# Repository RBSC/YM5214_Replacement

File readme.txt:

--------------------------------------------------------------------------------
Yamaha YM5214 Emulator Board v1.0
Copyright (c) 2023-2026 RBSC
--------------------------------------------------------------------------------

About
-----

This project's goal was to emulate Yamaha's YM5214 MMC chip that is used in CX5M and similar MSX1 computers as a
memory controller. These chips start to fail in the recent years, so it's good to have an alternative to keep our
CX5Ms alive. The design of this circuit board was inspired by a similar project by MetalGear2, whose website can
be found here: http://mymsx2.free.fr/

Assembling and Installing
-------------------------

The board is relatively easy to assemble. Please make sure that you solder all necessary elements and then remove
all flux from the board. The Altera chip on the newly-assembled board must be programmed before use. To do that,
you need to buy a USB Blaster device that can be easily obtained from AliExpress and download the Quartus II
Programmer v15.0 software that can be downloaded from here:

https://sysadminmosaic.ru/en/quartus_ii/quartus_ii#quartusiiweb150

To successfully program the CPLD, you must supply 5 Volts to the board. This can be done using a standard USB-A
cable to which two wires with female Dupont-type connectors have been soldered instead of the miniUSB or microUSB
connector. A cable with broken miniUSB or MicroUSB connector will do fine.

To program the CPLD it is not necessary to solder the JTAG connector or a pin header to the board. It is sufficient
to insert a 2x5-pin header into the "female" connector of the USB Blaster programmer, plug it into the JTAG
connector on the board, and bend it slightly for better contact with the board.

To power the board connect +5V to pin 10 on the YM5214's pin header and connect GND (ground) to pin 1. After that
you can connect the USB Blaster to the JTAG connector. Mind the correct orientation! Now you are ready to program
the CPLD chip.

Select the JTAG mode in the Quartus Programmer software and click the Auto-Detect button. If everything is assembled
and connected correctly, Quartus will detect the EPM240 chip. Next, place the cursor onto the firmware control line
(the one with "EPM240" string), right-click, and select the "Change File" option. A file selection window will
appear. Locate the firmware you need: it can be found in the Firmware folder. Select the .POF file with the firmware
and open it. Set the "Program/Configure," "Verify," and "Blank check" options and click the "Start" button to start
programming.

The CPLD programming usually takes less than a minute. A sign of successful programming is when the progress bar
reaches 100% and no errors appear in the lower window of the user interface. Once the CPLD programming is complete,
first disconnect the programmer and then disconnect the power cable from the board. The board is now fully ready
for use.

To install the board into the CX5M, first remove the broken YM5214 chip and install a 40-pin socket. Do not use sockets
with round pins unless you soldered round pin headers onto the curcuit board. Then carefully insert the curcuit board
into the socket and make sure it sits there firmly. Mind the orientation of the board! When powered on, your CX5M
should boot up in Basic and show 28kb of available RAM if the board is working correctly.

If you are unsure how to interpret or follow the above instructions, then it's advised to ask a more experienced
person for help.

IMPORTANT!
----------

The RBSC provides all the files and information for free, without any liability (see the disclaimer.txt file). The
provided information, software or hardware must not be used for commercial purposes unless permitted by the RBSC.
Producing a small amount of bare boards for personal projects and selling the rest of the batch is allowed without
the permission of RBSC.

When the sources of the tools are used to create alternative projects, please always mention the original source and
the copyright!

Contact information
-------------------

The members of RBSC group Tnt23, Wierzbowsky, Pyhesty, Ptero, GreyWolf, SuperMax, VWarlock, ALSP and DJS3000 can be
contacted via the group's e-mail address:

info@rbsc.su

The group's coordinator could be reached via this e-mail address:

admin@rbsc.su

The group's website can be found here:

https://rbsc.su/
https://rbsc.su/ru

The RBSC's hardware repository can be found here:

https://github.com/rbsc

The RBSC's 3D model repository can be found here:

https://www.thingiverse.com/groups/rbsc/things

-= ! MSX FOREVER ! =-

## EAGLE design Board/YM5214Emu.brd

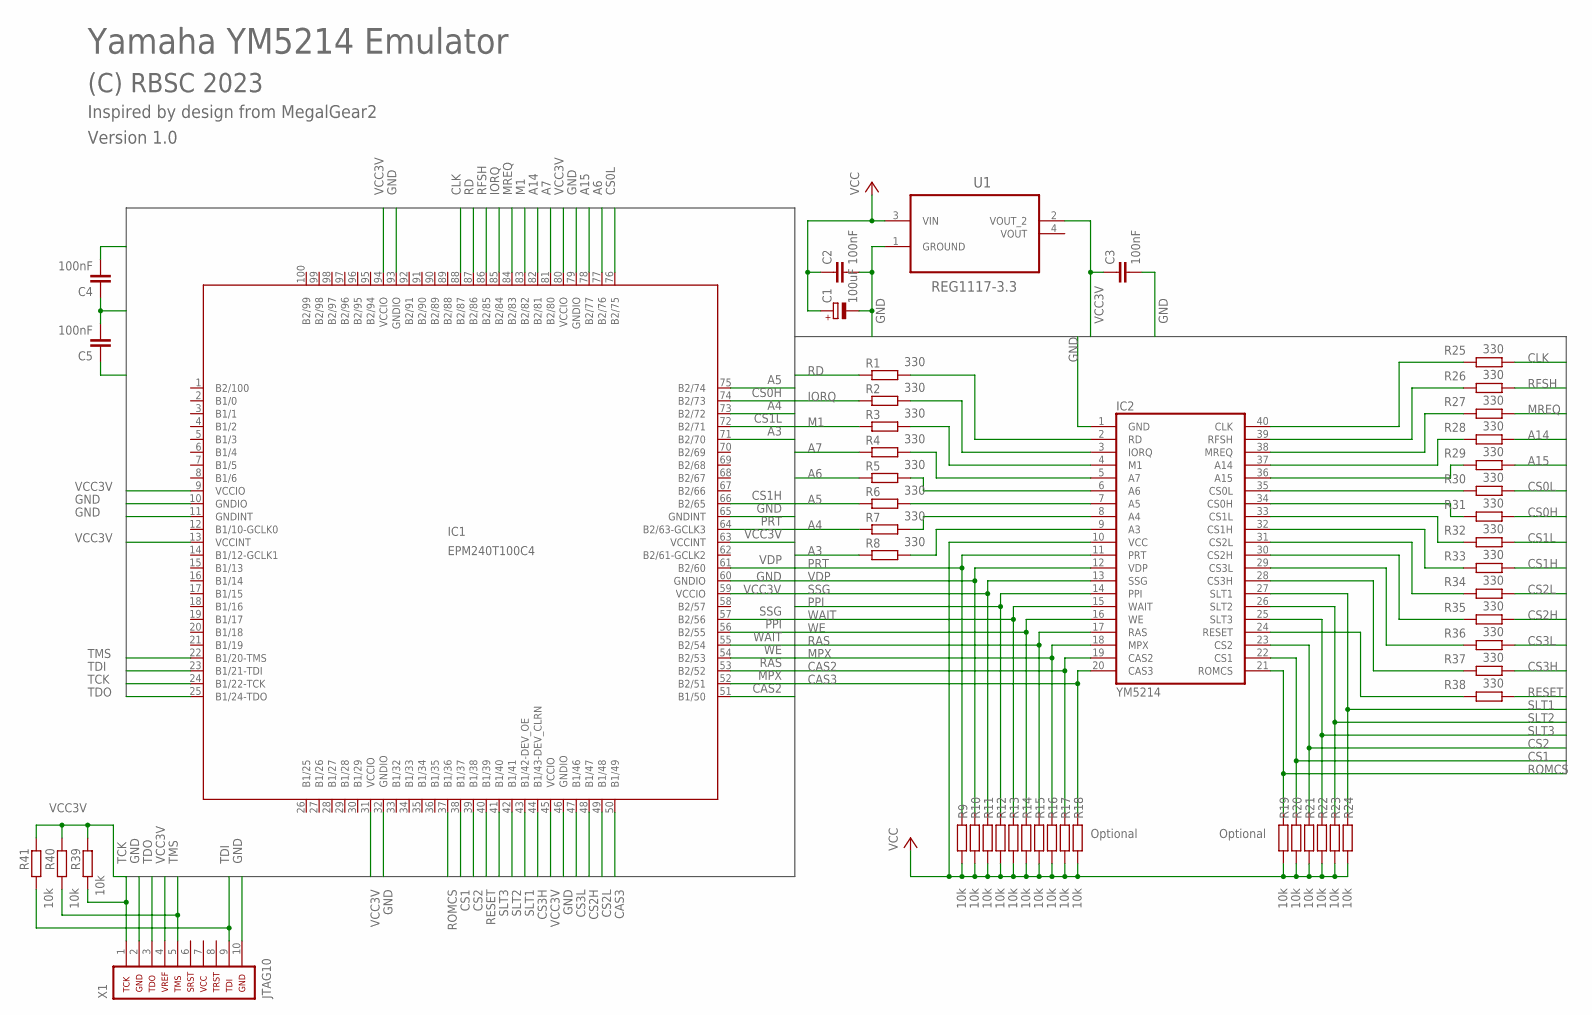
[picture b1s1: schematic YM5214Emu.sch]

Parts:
C1: 100uF; SMC_D
C2, C3, C4, C5: 100nF; C0805
IC1: EPM240T100C4; TQFP100
IC2: YM5214; DIL40
R1, R2, R3, R4, R5, R6, R7, R8, R25, R26, R27, R28, R29, R30, R31, R32, R33, R34, R35, R36, R37, R38: 330; R0805
R9, R10, R11, R12, R13, R14, R15, R16, R17, R18, R19, R20, R21, R22, R23, R24, R39, R40, R41: 10k; R0805
U1: REG1117-3.3; SOT230P700X180-4N
X1: JTAG10

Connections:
A3: IC1.71 (B2/70), R8.1
A4: IC1.73 (B2/72), R7.1
A5: IC1.75 (B2/74), R6.1
A6: IC1.77 (B2/76), R5.1
A7: IC1.81 (B2/80), R4.1
A14: IC1.82 (B2/81), R28.2
A15: IC1.78 (B2/77), R29.2
CAS2: IC1.51 (B1/50), IC2.19 (CAS2), R17.2
CAS3: IC1.50 (B1/49), IC2.20 (CAS3), R18.2
CLK: IC1.88 (B2/87), R25.2
CS0H: IC1.74 (B2/73), R31.2
CS0L: IC1.76 (B2/75), R30.2
CS1: IC1.38 (B1/37), IC2.22 (CS1), R20.2
CS1H: IC1.66 (B2/65), R33.2
CS1L: IC1.72 (B2/71), R32.2
CS2: IC1.39 (B1/38), IC2.23 (CS2), R21.2
CS2H: IC1.48 (B1/47), R35.2
CS2L: IC1.49 (B1/48), R34.2
CS3H: IC1.44 (B1/43-DEV_CLRN), R37.2
CS3L: IC1.47 (B1/46), R36.2
GND: C1.-, C2.2, C3.2, C4.1, C5.2, IC1.10 (GNDIO), IC1.11 (GNDINT), IC1.32 (GNDIO), IC1.46 (GNDIO), IC1.60 (GNDIO), IC1.65 (GNDINT), IC1.79 (GNDIO), IC1.93 (GNDIO), IC2.1 (GND), U1.1 (GROUND), X1.2, X1.10
IORQ: IC1.85 (B2/84), R2.1
M1: IC1.83 (B2/82), R3.1
MPX: IC1.52 (B2/51), IC2.18 (MPX), R16.2
MREQ: IC1.84 (B2/83), R27.2
unnamed: IC2.2 (RD), R1.2
unnamed: IC2.3 (IORQ), R2.2
unnamed: IC2.4 (M1), R3.2
unnamed: IC2.5 (A7), R4.2
unnamed: IC2.6 (A6), R5.2
unnamed: IC2.7 (A5), R6.2
unnamed: IC2.8 (A4), R7.2
unnamed: IC2.9 (A3), R8.2
unnamed: IC2.24 (RESET), R38.1
unnamed: IC2.28 (CS3H), R37.1
unnamed: IC2.29 (CS3L), R36.1
unnamed: IC2.30 (CS2H), R35.1
unnamed: IC2.31 (CS2L), R34.1
unnamed: IC2.32 (CS1H), R33.1
unnamed: IC2.33 (CS1L), R32.1
unnamed: IC2.34 (CS0H), R31.1
unnamed: IC2.35 (CS0L), R30.1
unnamed: IC2.36 (A15), R29.1
unnamed: IC2.37 (A14), R28.1
unnamed: IC2.38 (MREQ), R27.1
unnamed: IC2.39 (RFSH), R26.1
unnamed: IC2.40 (CLK), R25.1
PPI: IC1.56 (B2/55), IC2.14 (PPI), R12.2
PRT: IC1.64 (B2/63-GCLK3), IC2.11 (PRT), R9.2
RAS: IC1.53 (B2/52), IC2.17 (RAS), R15.2
RD: IC1.87 (B2/86), R1.1
RESET: IC1.40 (B1/39), R38.2
RFSH: IC1.86 (B2/85), R26.2
ROMCS: IC1.37 (B1/36), IC2.21 (ROMCS), R19.2
SLT1: IC1.43 (B1/42-DEV_OE), IC2.27 (SLT1), R24.2
SLT2: IC1.42 (B1/41), IC2.26 (SLT2), R23.2
SLT3: IC1.41 (B1/40), IC2.25 (SLT3), R22.2
SSG: IC1.57 (B2/56), IC2.13 (SSG), R11.2
TCK: IC1.24 (B1/22-TCK), R39.1, X1.1
TDI: IC1.23 (B1/21-TDI), R41.1, X1.9
TDO: IC1.25 (B1/24-TDO), X1.3
TMS: IC1.22 (B1/20-TMS), R40.1, X1.5
VCC: C1.+, C2.1, IC2.10 (VCC), R9.1, R10.1, R11.1, R12.1, R13.1, R14.1, R15.1, R16.1, R17.1, R18.1, R19.1, R20.1, R21.1, R22.1, R23.1, R24.1, U1.3 (VIN)
VCC3V: C3.1, C4.2, C5.1, IC1.9 (VCCIO), IC1.13 (VCCINT), IC1.31 (VCCIO), IC1.45 (VCCIO), IC1.59 (VCCIO), IC1.63 (VCCINT), IC1.80 (VCCIO), IC1.94 (VCCIO), R39.2, R40.2, R41.2, U1.2 (VOUT_2), X1.4
VDP: IC1.61 (B2/60), IC2.12 (VDP), R10.2
WAIT: IC1.55 (B2/54), IC2.15 (WAIT), R13.2
WE: IC1.54 (B2/53), IC2.16 (WE), R14.2

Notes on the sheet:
Optional
(C) RBSC 2023
Version 1.0
Inspired by design from MegalGear2
Yamaha YM5214 Emulator

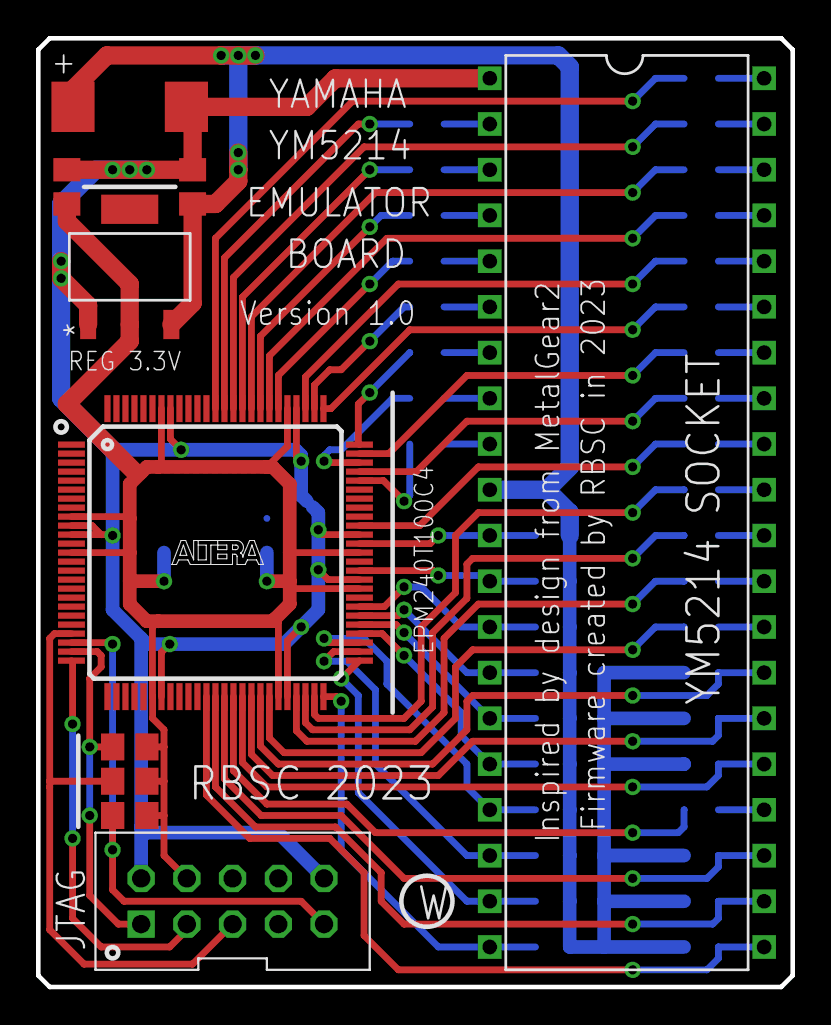
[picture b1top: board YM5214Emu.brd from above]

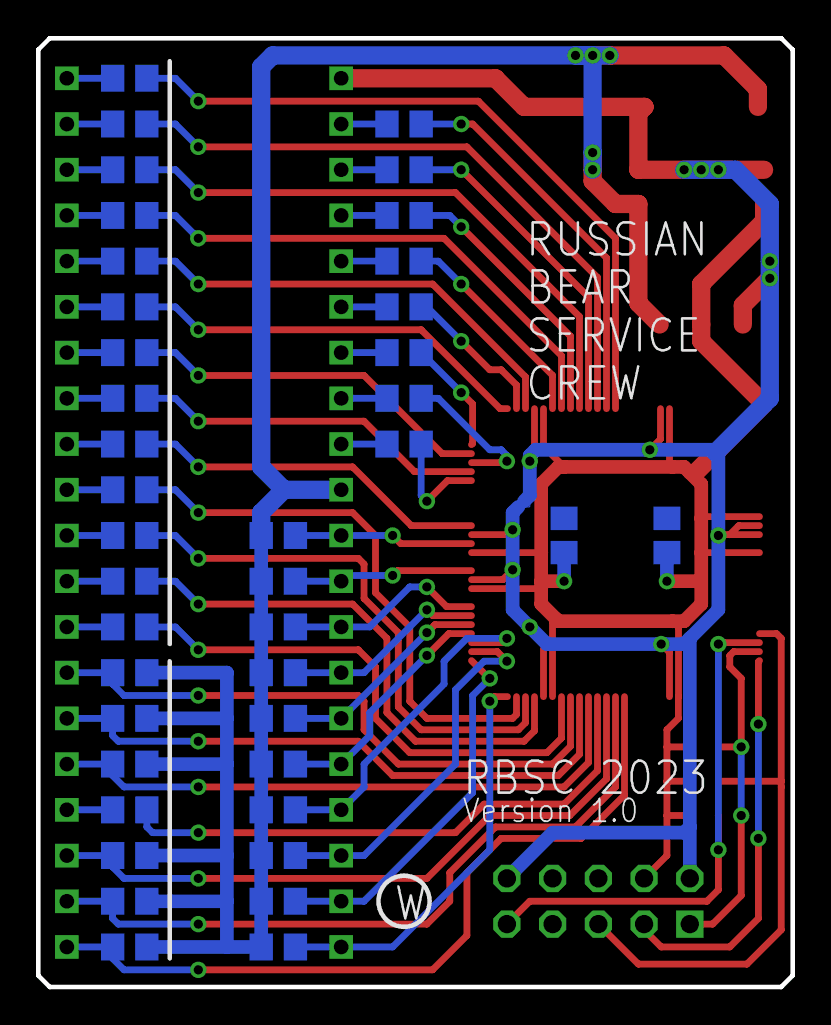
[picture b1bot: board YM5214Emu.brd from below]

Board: 2 copper layers, 41.9 x 52.7 mm, 50 parts (40 on the bottom side), 67 nets.

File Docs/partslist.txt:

Partlist
--------

Part     Value          Device       Package

C1       100uF          CPOL-EUSMCD  SMC_D
C2       100nF          C-EUC0805    C0805
C3       100nF          C-EUC0805    C0805
C4       100nF          C-EUC0805    C0805
C5       100nF          C-EUC0805    C0805
IC1      EPM240T100C4   EPM240T100C4 TQFP100
CN1      YM5214         YM5214       DIL40
R1       330            R-EU_R0805   R0805
R2       330            R-EU_R0805   R0805
R3       330            R-EU_R0805   R0805
R4       330            R-EU_R0805   R0805
R5       330            R-EU_R0805   R0805
R6       330            R-EU_R0805   R0805
R7       330            R-EU_R0805   R0805
R8       330            R-EU_R0805   R0805
R9       10k            R-EU_R0805   R0805
R10      10k            R-EU_R0805   R0805
R11      10k            R-EU_R0805   R0805
R12      10k            R-EU_R0805   R0805
R13      10k            R-EU_R0805   R0805
R14      10k            R-EU_R0805   R0805
R15      10k            R-EU_R0805   R0805
R16      10k            R-EU_R0805   R0805
R17      10k            R-EU_R0805   R0805
R18      10k            R-EU_R0805   R0805
R19      10k            R-EU_R0805   R0805
R20      10k            R-EU_R0805   R0805
R21      10k            R-EU_R0805   R0805
R22      10k            R-EU_R0805   R0805
R23      10k            R-EU_R0805   R0805
R24      10k            R-EU_R0805   R0805
R25      330            R-EU_R0805   R0805
R26      330            R-EU_R0805   R0805
R27      330            R-EU_R0805   R0805
R28      330            R-EU_R0805   R0805
R29      330            R-EU_R0805   R0805
R30      330            R-EU_R0805   R0805
R31      330            R-EU_R0805   R0805
R32      330            R-EU_R0805   R0805
R33      330            R-EU_R0805   R0805
R34      330            R-EU_R0805   R0805
R35      330            R-EU_R0805   R0805
R36      330            R-EU_R0805   R0805
R37      330            R-EU_R0805   R0805
R38      330            R-EU_R0805   R0805
R39      10k            R-EU_R0805   R0805
R40      10k            R-EU_R0805   R0805
R41      10k            R-EU_R0805   R0805
U1       REG1117-3.3    REG1117-3.3  SOT230P700X180-4N
X1       JTAG10         JTAG10       JTAG

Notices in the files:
parts and their libraries:
JTAG: Copyright (C) 2010 Michel Catudal mcatudal@comcast.net
